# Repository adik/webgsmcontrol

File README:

TAGS: SIM900, GPRS, Arduino, PushAPP, WebSockets

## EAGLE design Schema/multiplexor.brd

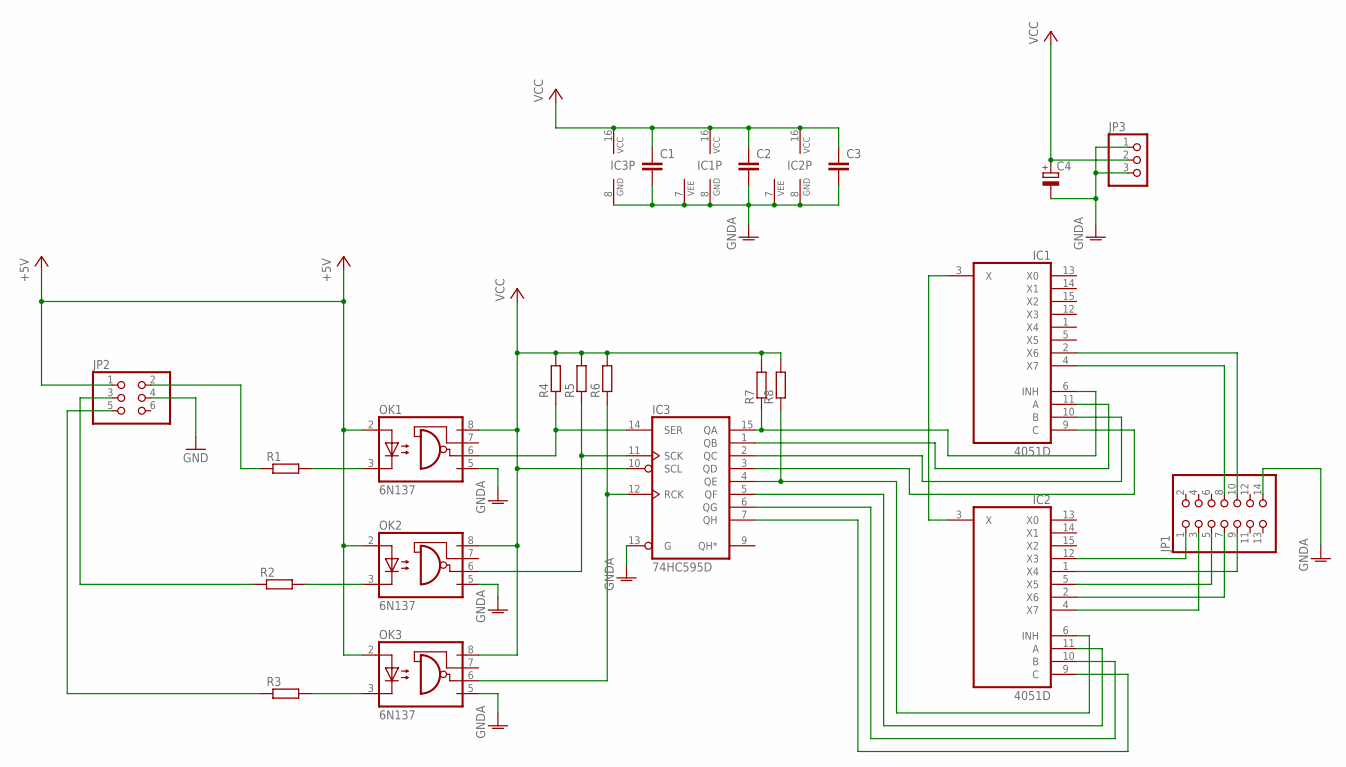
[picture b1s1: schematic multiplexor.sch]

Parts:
C1, C2, C3: C-EUC1206K; C1206K
C4: CPOL-EUE2.5-6; E2,5-6
IC1, IC2: 4051D; SO16
IC3: 74HC595D; SO16
JP1: PINHD-2X7; 2X07
JP2: PINHD-2X3; 2X03
JP3: PINHD-1X3; 1X03
OK1, OK2, OK3: 6N137; DIL08
R1, R2, R3, R4, R5, R6, R7, R8: R-EU_R1206; R1206

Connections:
+5V: JP2.1, OK1.2 (A), OK2.2 (A), OK3.2 (A)
GND: JP2.4
GNDA: C1.2, C2.2, C3.2, C4.-, IC1.7 (VEE), IC1.8 (GND), IC2.7 (VEE), IC2.8 (GND), IC3.8 (GND), IC3.13 (G), JP1.14, JP3.1, JP3.3, OK1.5 (GND), OK2.5 (GND), OK3.5 (GND)
unnamed: IC1.6 (INH), IC3.15 (QA), R7.1
unnamed: IC1.11 (A), IC3.1 (QB)
unnamed: IC1.10 (B), IC3.2 (QC)
unnamed: IC1.9 (C), IC3.3 (QD)
unnamed: IC2.6 (INH), IC3.4 (QE), R8.1
unnamed: IC2.11 (A), IC3.5 (QF)
unnamed: IC2.10 (B), IC3.6 (QG)
unnamed: IC2.9 (C), IC3.7 (QH)
unnamed: IC1.3 (X), IC2.3 (X)
unnamed: IC1.2 (X6), JP1.10
unnamed: IC2.12 (X3), JP1.1
unnamed: IC1.4 (X7), JP1.8
unnamed: IC2.4 (X7), JP1.3
unnamed: IC2.5 (X5), JP1.5
unnamed: IC2.2 (X6), JP1.7
unnamed: IC2.1 (X4), JP1.9
unnamed: OK1.3 (C), R1.2
unnamed: OK2.3 (C), R2.2
unnamed: OK3.3 (C), R3.2
unnamed: IC3.14 (SER), OK1.6 (VO), R4.1
unnamed: IC3.11 (SCK), OK2.6 (VO), R5.1
unnamed: IC3.12 (RCK), OK3.6 (VO), R6.1
unnamed: JP2.2, R1.1
unnamed: JP2.3, R2.1
unnamed: JP2.5, R3.1
VCC: C1.1, C2.1, C3.1, C4.+, IC1.16 (VCC), IC2.16 (VCC), IC3.10 (SCL), IC3.16 (VCC), JP3.2, OK1.8 (VCC), OK2.8 (VCC), OK3.8 (VCC), R4.2, R5.2, R6.2, R7.2, R8.2

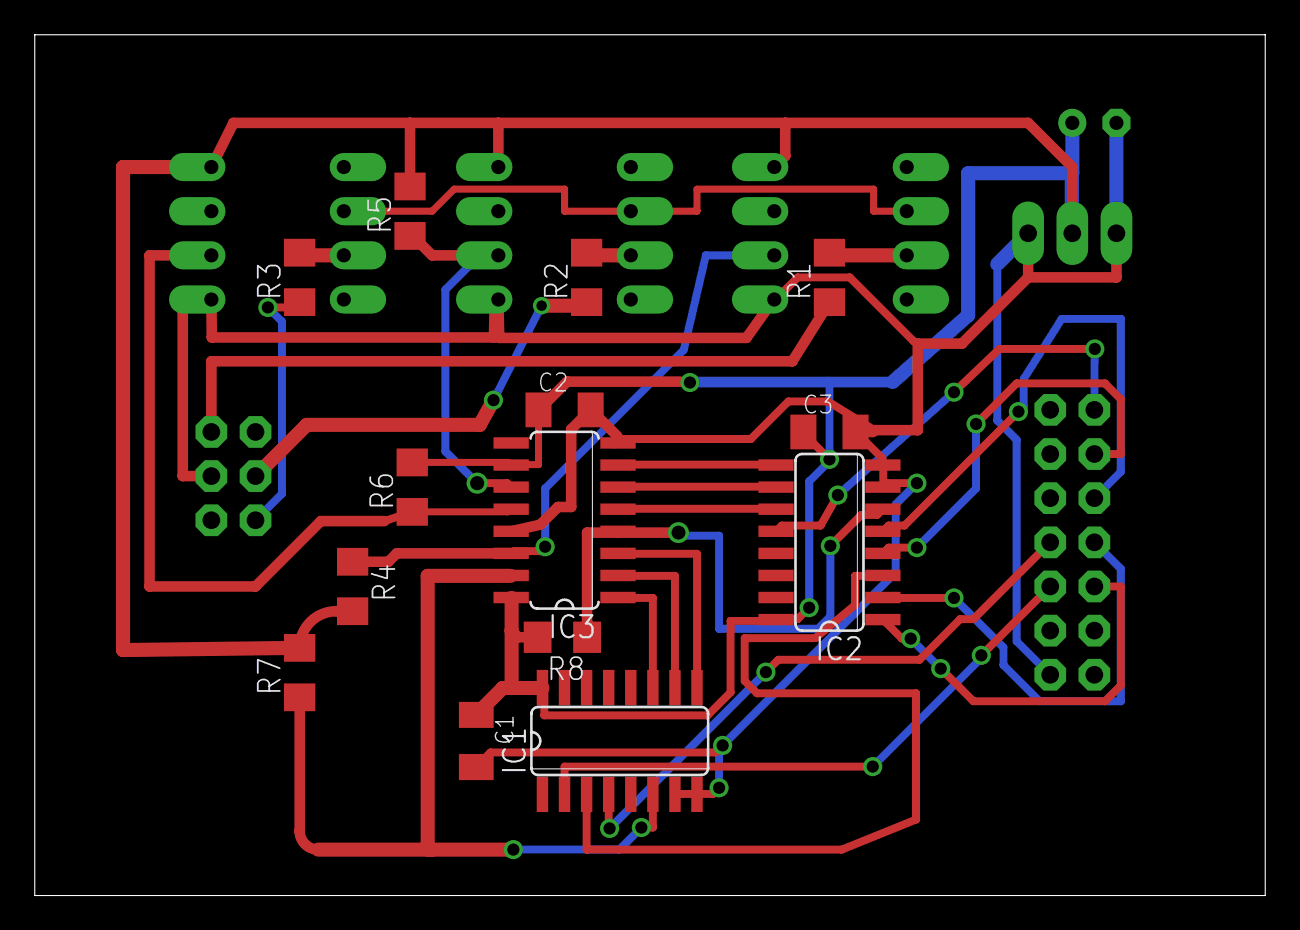
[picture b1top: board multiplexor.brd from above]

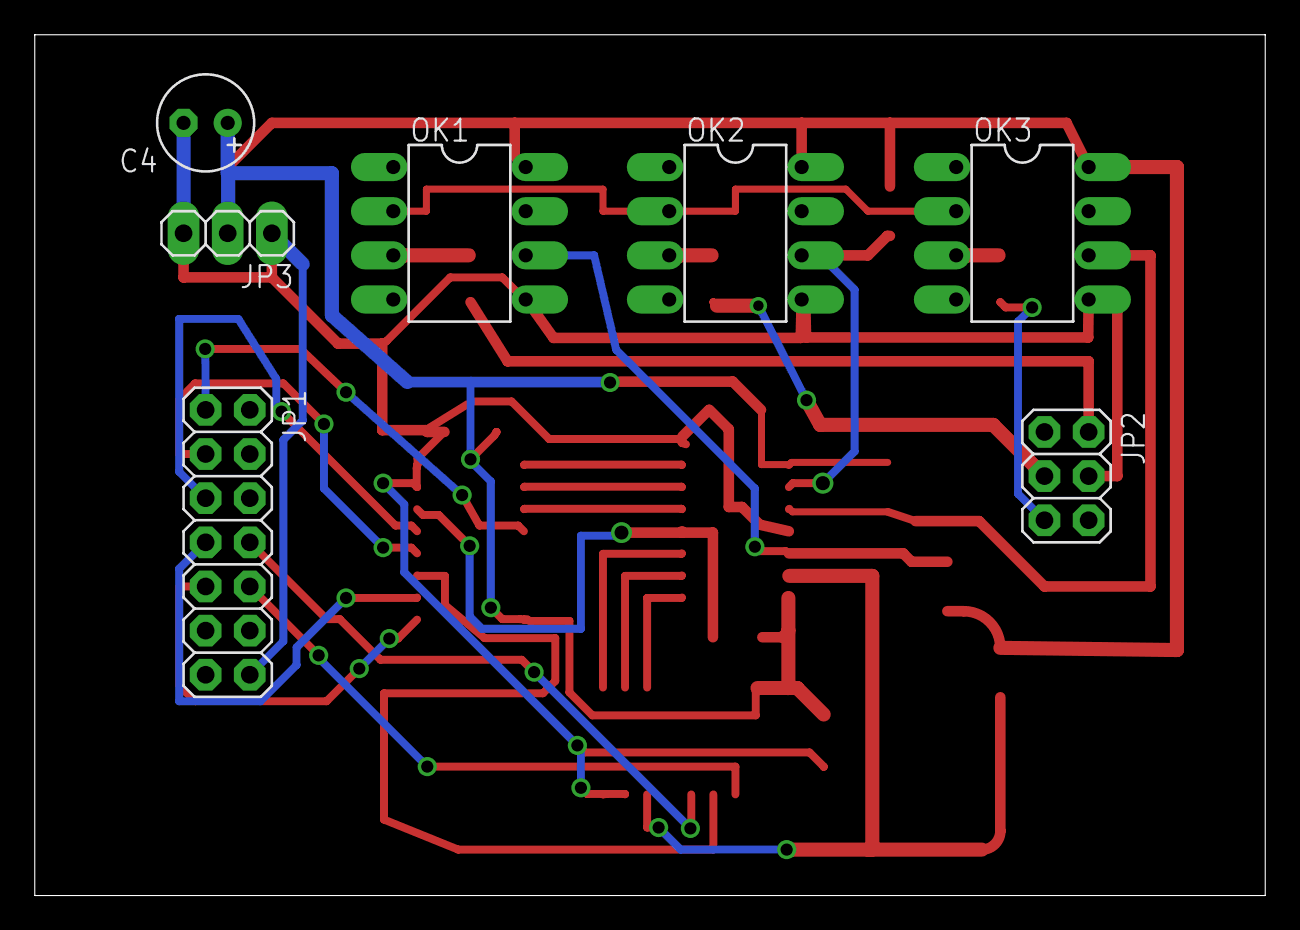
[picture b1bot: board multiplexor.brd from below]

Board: 2 copper layers, 70.8 x 49.5 mm, 21 parts (7 on the bottom side), 28 nets.

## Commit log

2012-08-22 INIT
2012-08-26 snapshot
2012-08-26 add recv callback to SoftwareSerial
2012-08-31 snap
2012-08-31 next
2012-09-03 change receive alghoritm
2012-09-03 Remove software serial recv handler
2012-09-05 update lib
2012-09-05 add SHA256
2012-09-09 release 0.1-rc
2012-09-09 fix mistakes
2012-09-09 add support ping-pong (protocol version 5)
2012-10-29 add schema
2013-03-13 Next release
2013-03-13 remove garbage
2014-12-25 compatility with new Arduino library, schema update...
